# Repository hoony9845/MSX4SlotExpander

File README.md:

# MSX拡張Cartridge<BR>4Slot Expander Cartridge  

MSX スロットを4つに増やす拡張ユニットです。

> v2(バスバッファ付き・50pin IDCケーブル接続・大宇MSX後面スロット互換)の設計は [docs/expander_v2.md](./docs/expander_v2.md) を参照。

MSX規格の拡張スロット仕様に準拠した4スロットユニットです。  
信頼性が必要なカードエッジコネクタは、AMP 5530843-5または5530841-5を使用しています。  

Simple2Slot Expanderのサブセットで、本来の拡張スロットユニットに必要なバスバッファ・電源・音声ミキシング回路を省略することで安価になるように設計しました。  
そのため、個々のスロットは以下のMSX規格を守れていません。  

本基板および各オプションは、家電のKENちゃんおよびBEEPにて頒布を予定しています。    

## ■ 利用上の注意点  

構造上、誰がみても機械的に無理があるので縦差しでの使用はおすすめしません＾＾；  

バスバッファー回路が無い都合上、ファンアウトがMSXスロット規格を満たしていません、  
そのため本体およびカートリッジの組み合わせによる相性が出る場合があります。  

各スロットの電源容量は、本体に依存します。  
電力消費が大きいカートリッジでは動作しない可能性があります。  
規格上は合計で5V 100mAまでです、必要に応じて外部電源モードを使ってください。    
BUSDIR信号には対応しているので、IO系カセットも正常に動作します。

### 動作確認のスロット構成
当方の検証では下記機種、下記構成にて、全スロットへのRead/Writeが確認できています。
```
#X-1 ROM + Memory Mapper 1Mbyte
#X-2 DRAM 64K
#X-3 SCC Cartridge
#X-4 Flash ROM (TEST PROGRAM)
```
  
### 動作確認機種
MSX
- CASIO PV-16　（※外部電源モード）
- FUJITSU FM-X
- TOSHIBA HX-10
- Panasonic CF-1000
- Panasonic CF-3000  

MSX2  
- Panasonic FS-4600
- Panasonic FS-A1F
- TOSHIBA HX-34  
- D4D 1chip MSX

MSX2+
- SONY HB-F1XDJ
- SONY HB-F1XV
- SANYO WAVY 70

MSX Turbo R
- Panasonic FS-A1ST
- Panasonic FS-A1GT

### 不具合が合った機種
下記機種は、動作不良があった機種です。

MSX2  
- SONY HB-F500 　(オプションの延長ケーブルの使用時)
- SONY HB-F900 　(オプションの延長ケーブルの使用時)
- CANON V30

## ■ 頒布先
### 家電のKENちゃん
MSX Simple 4 Slot Expander【完成品】  
https://www.kadenken.com/view/item/000000001635  

●オプション  
加工済シェルケース(RGR製)  
クリアブラック　 :  https://www.kadenken.com/view/item/000000001318  
クリア　　　　 : https://www.kadenken.com/view/item/000000001317  

MSX Slot 延長ケーブル : https://www.kadenken.com/view/item/000000001636  

### BEEP
MSX Simple 4 Slot Expander【完成品】  
https://www.beep-shop.com/ec/products/detail/38517  

●オプション  
加工済シェルケース(RGR製)  
ブラック　　　 :  https://www.beep-shop.com/ec/products/detail/38515  
クリアブラック　 : https://www.beep-shop.com/ec/products/detail/38514  

MSX Slot 延長ケーブル : https://www.beep-shop.com/ec/products/detail/38516  

## ■ 付属品
本体には下記が付属しています。  
  
- ゴム足 　　　　　x 4個
- 専用スペーサー　　 x 2個
- タッピングビス(長)　 x 4個
- タッピングビス(短)　 x 4個  
### 付属品の使い方
直接本体のスロットに挿入する場合は、専用スペーサーをネジ止めして取り付けてください。  
オプションの延長ケーブルを使う場合は基板の裏面にゴム足を貼り付けて使用することも可能です。  
### 専用スペーサについて
固定には、スロットコネクタの左右の穴にタッピングビスを使って固定してください。

スロットコネクタは入手の都合で2種類あり、固定部があるものと無いものがあります。  
固定部があるものは長いタッピングビスを、無いものは短いタッピングビスを使って固定してください。  

使用時は脚部のネジを回して本体のスロットの高さに本製品を合わせてお使いください。

## ■ 使用方法

通常のカートリッジ同様に電源を切ったMSXスロットに挿入してください。  
カートリッジは、正面が下側になるように本基板スロットに挿入してください。

## ■ メモリマップ

MSXの拡張スロット仕様準拠です。

## ■ 頒布基板について
基板上のスイッチおよびジャンパの機能は下記の通りです。  

|Ref No|Name|機能|
| :- |  :- |  :- | 
|S1|SLTSEL(SLOT3)|SLOT3の切り離しスイッチです。<BR>つまみを下にするとカセットを切り離せます|
|S2|SLTSEL(SLOT2)|SLOT2の切り離しスイッチです。<BR>つまみを下にするとカセットを切り離せます|
|S3|SLTSEL(SLOT1)|SLOT1の切り離しスイッチです。<BR>つまみを下にするとカセットを切り離せます|
|S4|SLTSEL(SLOT0)|SLOT0の切り離しスイッチです。<BR>つまみを下にするとカセットを切り離せます|
|J5|POWER SETTING|スロットの5V電源を供給先を選択するジャンパです。<BR>INT側でMSX本体から、EXT側でDCジャックから供給します。|
|CN1 |DCジャック|Φ2.1 5Vセンタープラスのアダプタを接続します。|
|CN2 |SOUNDOUT（SLOT0)|SLOT0のサウンド出力です(オプション)|
|CN4 |SOUNDOUT（SLOT1)|SLOT1のサウンド出力です(オプション)|
|CN9 |SOUNDOUT（SLOT2)|SLOT2のサウンド出力です(オプション)|
|CN10 |SOUNDOUT（SLOT3)|SLOT3のサウンド出力です(オプション)|

回路図およびガーバファイルが必要な場合はPCBのフォルダーを参考にしてください。  

## ■ 外部電源供給について  
本製品はジャンパJ5を切り替えることでスロットの5V電源を外部供給に切り替えることが可能です。  
アダプタは、DCジャックは外径5.5mm内径2.1mm 電圧5V 500mA以上のアダプタを使用してください。  

下記の商品が使用できます。  

秋月電子　超小型スイッチングＡＣアダプター５Ｖ１Ａ  
https://akizukidenshi.com/catalog/g/gM-06096/

COMON DC-5521A + USB ACアダプタ   
http://www.comon.co.jp/DC-5521A.htm

## ■ サウンド出力について  
本製品はサウンドミキシング回路を搭載していません。SOUND IN端子は、4スロット間で直結しています。  
そのためサウンド出力を使うカートリッジを複数のスロットに挿さない様にしてください。
最悪の場合カートリッジを壊す可能性があります。

使用する場合はサウンド出力を使って、外部に接続したミキサーで音源を合成してください。  

### サウンド出力の使い方
DC入力近辺に、サウンド出力を追加するパターンを設けています。  
パーツは一般的なRCAジャックが使える様なパターンになっています。  
当該部にRCAジャックを半田付けしてください。  

推奨パーツ: 秋月電子　基板用ＲＣＡジャック（黒）  
https://akizukidenshi.com/catalog/g/gC-06509/

使用する場合は、J1-4 SOUNDジャンパの裏面パターンをカットしてください。  
裏面にジャンパを追加することで切り替え式にすることも可能です。(注意：表面だとカセットと接触します）  
なお、SLOT0のSOUNDジャンパ(J4)はシェルケールと干渉するので、そのまま使うのをおすすめします。  

### なぜミキシング回路をつけないのですか？
MSX本体の音声入力は規格で-5dbmと決められています。  
単純に4スロットの音声を全てミキシングしてしまうと出力は4倍になり規格違反になります。  
それを防ぐ為には、各スロットの音声を1/4する必要があるのですが、1つしか音声が入力を接続しないケースでは  
直接スロットに差すときと比較すると音声が非常に小さくなります。  
そこら辺の整合がとれないため、ミキシング回路は省略しています。

なお、市販されていたNEOS EX-4でもミキシング回路は入っておらず直結でした。

## ■ CPLDについて

CPLD Xillix XC9536XLの設計データはRTLのフォルダーを参照してください。  

## ■ (オプション)　MSXスロット延長ケーブル について
MSXのスロットを延長するケーブルです。(ケーブル長20cm)  
スロットに対する物理的な加重や構造的に無理がある場合にお使いください。  

なお本製品で使用しているカードエッジコネクタは大手メーカ製が廃盤になってしまっており、   
中国製のものを使用しています。そのため金メッキ品ですが長期信頼性は不明です。  
カートリッジシェルは本製品と同じものが使用できます。

使用時はコネクタに張ってある、シール側がカセット正面になるようにセットしてください。

## ■ (オプション)カートリッジシェル について
シェルケースは
RGRさんのTransparent Cartridge Shell for MSX Konami-styleを切削加工したものを使用しています。  
<https://retrogamerestore.com/store/msx_cart_shell/>  

当方でも加工済みシェルを用意しており、委託先で購入が可能です。  
輸入と加工の都合で若干の小傷がある場合があります。あらかじめご了承ください。  

切削加工部分については、下記図面を参照ください。（ハッチ部分が切削箇所）

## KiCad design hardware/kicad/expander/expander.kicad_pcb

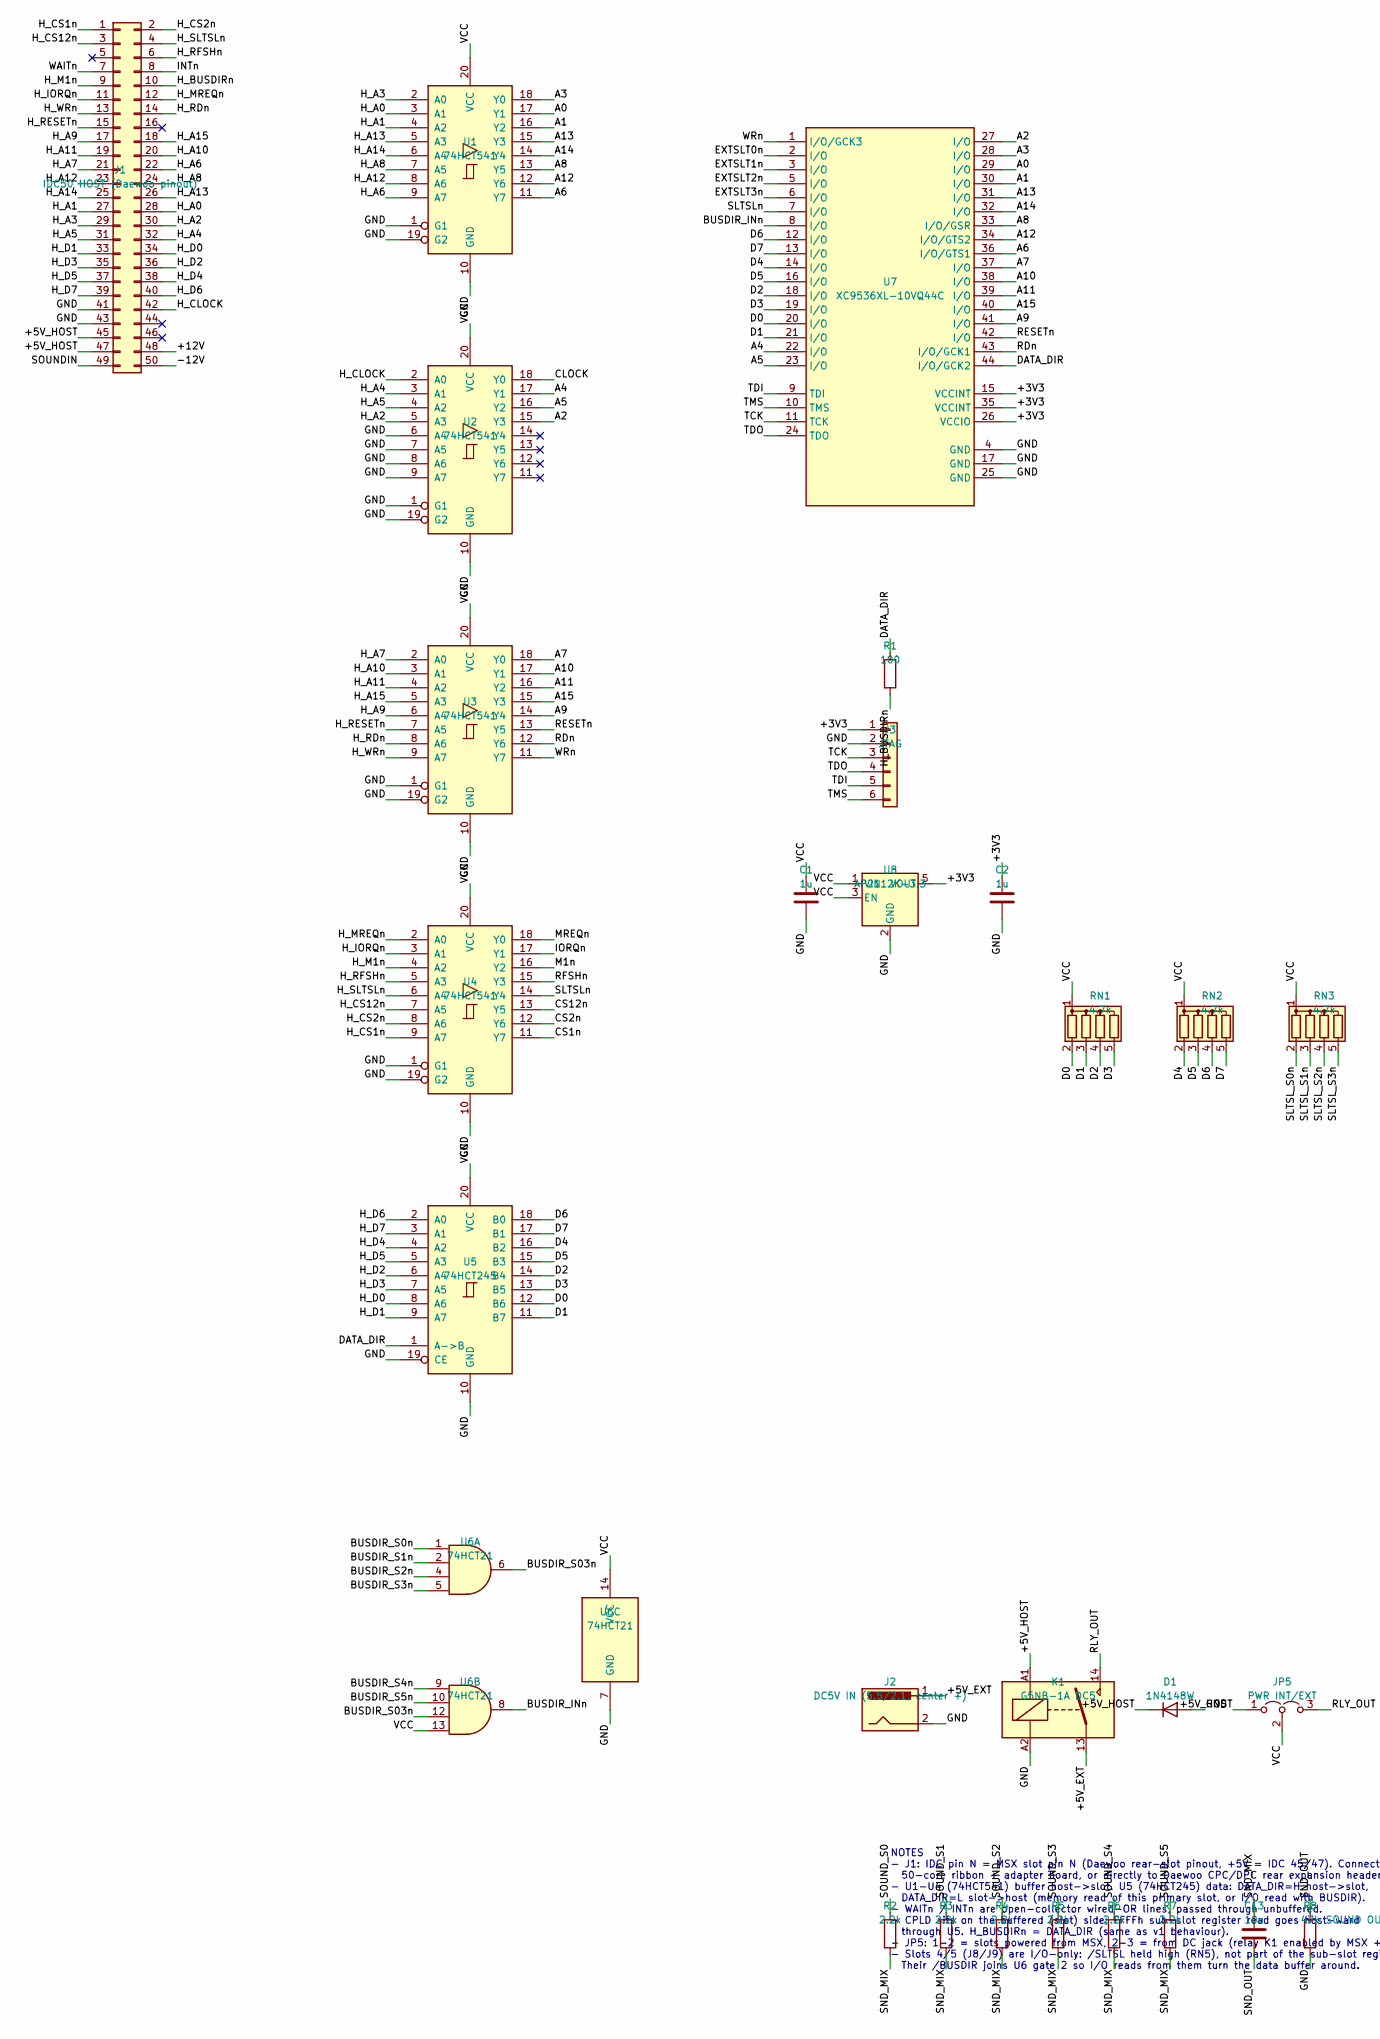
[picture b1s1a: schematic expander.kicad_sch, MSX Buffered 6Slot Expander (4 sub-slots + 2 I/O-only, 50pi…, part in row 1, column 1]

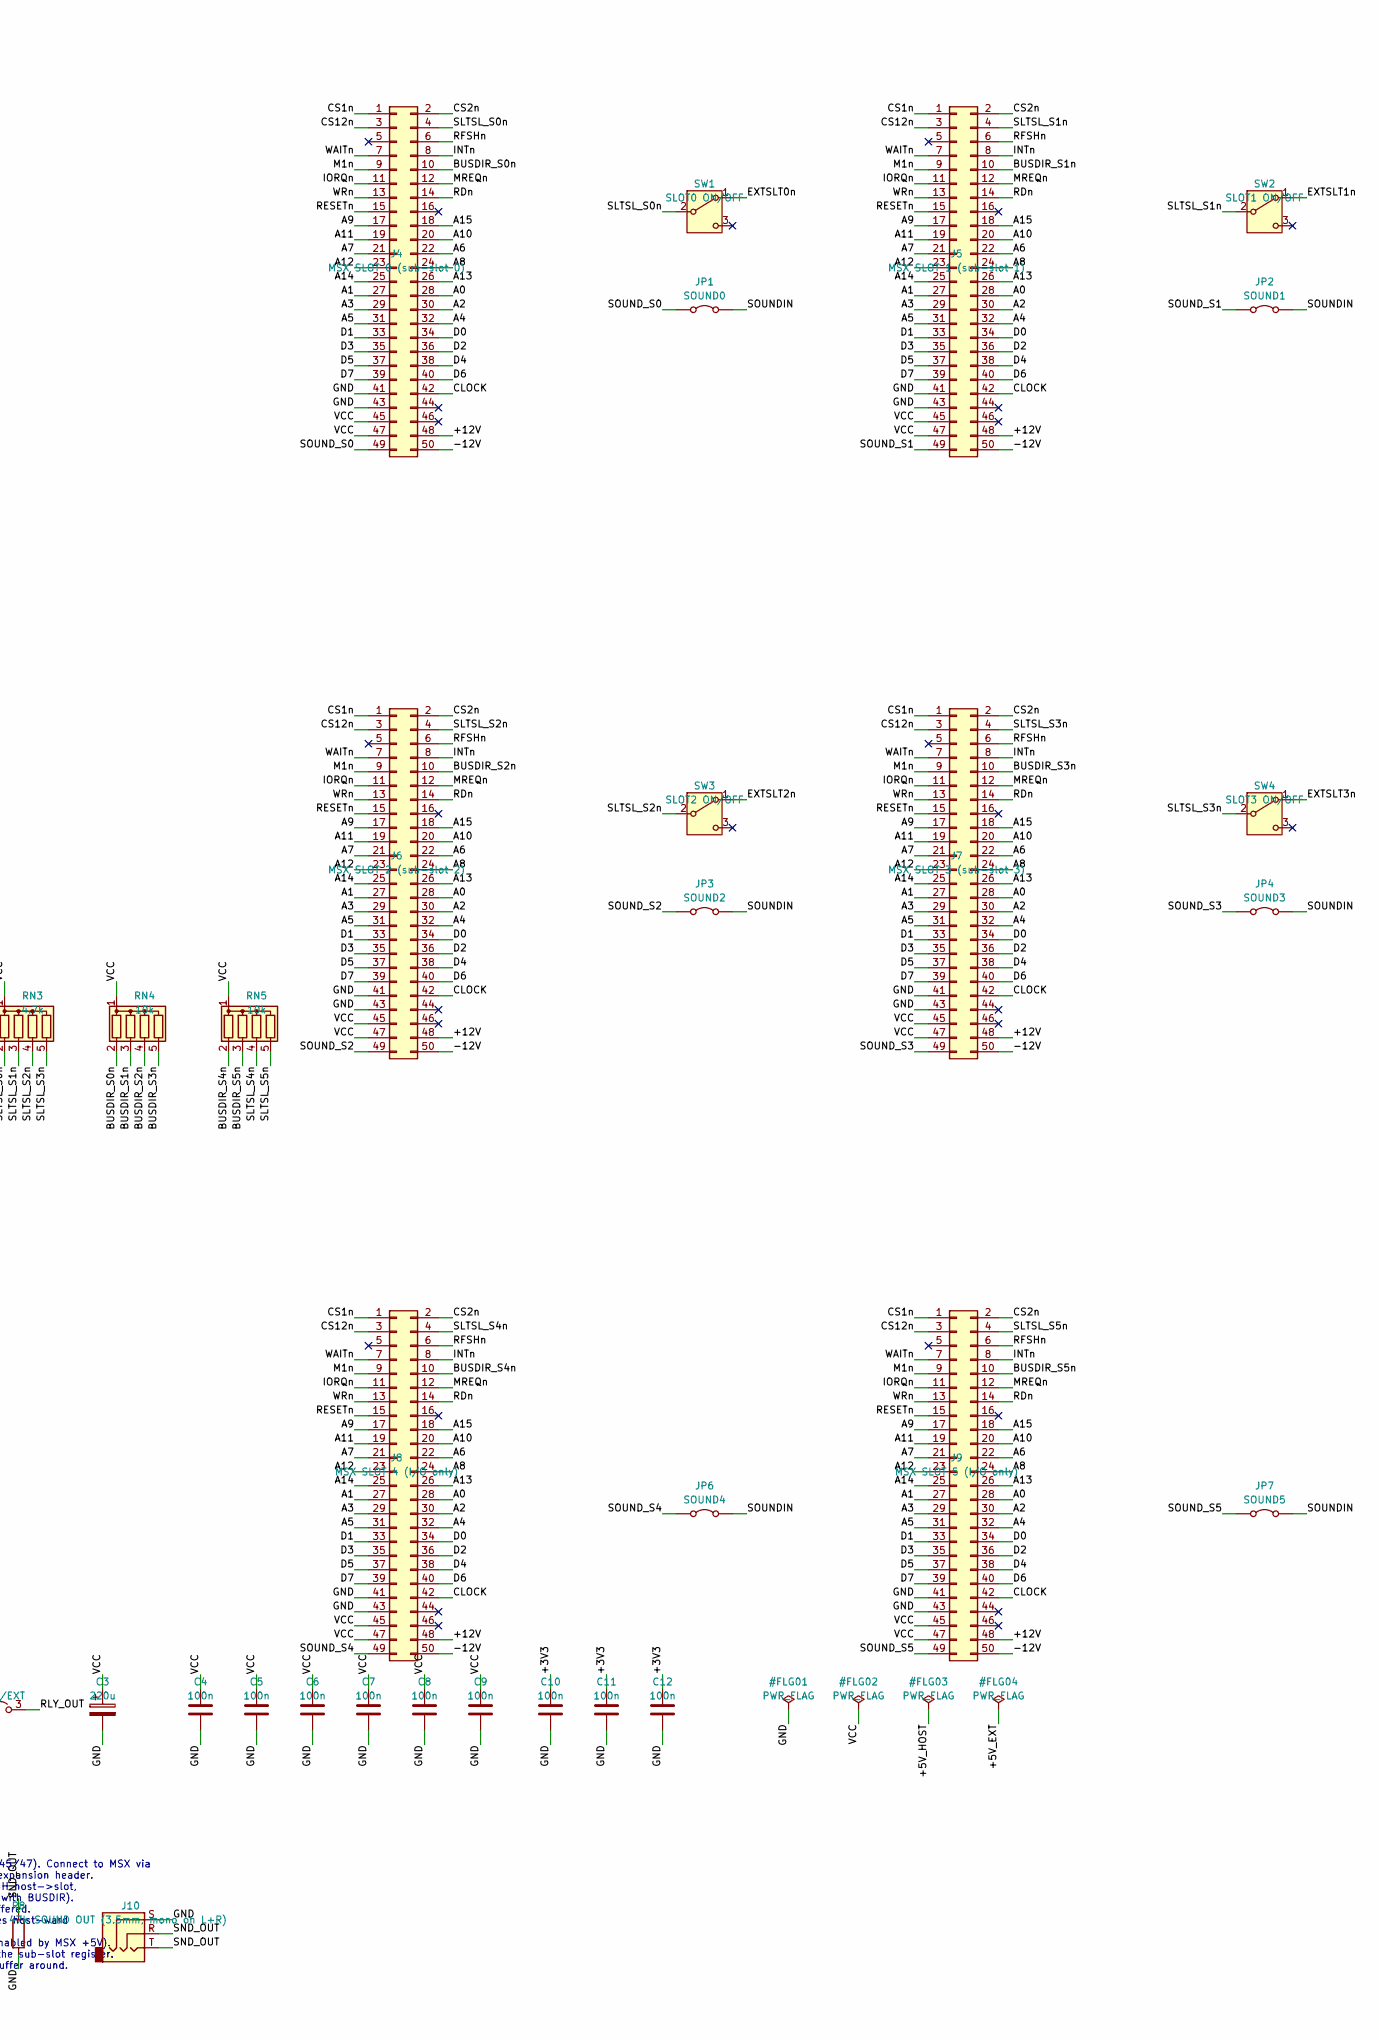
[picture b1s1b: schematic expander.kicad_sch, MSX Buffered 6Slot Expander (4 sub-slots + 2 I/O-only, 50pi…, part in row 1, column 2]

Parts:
C1, C2: 1u; C_0805_2012Metric
C3: 220u; CP_Radial_D6.3mm_P2.50mm
C4, C5, C6, C7, C8, C9, C10, C11, C12: 100n; C_0805_2012Metric
C13: 10u; C_0805_2012Metric
D1: 1N4148W; D_SOD-123
J1: IDC50 HOST (Daewoo pinout); IDC-Header_2x25_P2.54mm_Horizontal_OddRowFront
J2: DC5V IN (5.5/2.1, center +); BarrelJack_Horizontal
J3: JTAG; PinHeader_1x06_P2.54mm_Vertical
J4: MSX SLOT 0 (sub-slot 0); MSX_Slot_AMP5530843
J5: MSX SLOT 1 (sub-slot 1); MSX_Slot_AMP5530843
J6: MSX SLOT 2 (sub-slot 2); MSX_Slot_AMP5530843
J7: MSX SLOT 3 (sub-slot 3); MSX_Slot_AMP5530843
J8: MSX SLOT 4 (I/O only); MSX_Slot_AMP5530843
J9: MSX SLOT 5 (I/O only); MSX_Slot_AMP5530843
J10: SOUND OUT (3.5mm, mono on L+R); Jack_3.5mm_CUI_SJ1-3523N_Horizontal
JP1: SOUND0; PinHeader_1x02_P2.54mm_Vertical
JP2: SOUND1; PinHeader_1x02_P2.54mm_Vertical
JP3: SOUND2; PinHeader_1x02_P2.54mm_Vertical
JP4: SOUND3; PinHeader_1x02_P2.54mm_Vertical
JP5: PWR INT/EXT; PinHeader_1x03_P2.54mm_Vertical
JP6: SOUND4; PinHeader_1x02_P2.54mm_Vertical
JP7: SOUND5; PinHeader_1x02_P2.54mm_Vertical
K1: G5NB-1A DC5; Relay_SPST_Omron_G5NB
R1: 100; R_0805_2012Metric
R2, R3, R4, R5, R6, R7: 2.2k; R_0805_2012Metric
R8: 47k; R_0805_2012Metric
RN1, RN2, RN3: 4.7k; R_Array_SIP5
RN4, RN5: 10k; R_Array_SIP5
SW1: SLOT0 ON/OFF; SW_Slide_SPDT_Angled_CK_OS102011MA1Q
SW2: SLOT1 ON/OFF; SW_Slide_SPDT_Angled_CK_OS102011MA1Q
SW3: SLOT2 ON/OFF; SW_Slide_SPDT_Angled_CK_OS102011MA1Q
SW4: SLOT3 ON/OFF; SW_Slide_SPDT_Angled_CK_OS102011MA1Q
U1, U2, U3, U4: 74HCT541; SOIC-20W_7.5x12.8mm_P1.27mm
U5: 74HCT245; SOIC-20W_7.5x12.8mm_P1.27mm
U6: 74HCT21; SOIC-14_3.9x8.7mm_P1.27mm
U7: XC9536XL-10VQ44C; TQFP-44_10x10mm_P0.8mm
U8: AP2112K-3.3; SOT-23-5

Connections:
/+3V3: C2.1, C10.1, C11.1, C12.1, J3.1, U7.15 (VCCINT), U7.26 (VCCIO), U7.35 (VCCINT), U8.5 (VOUT)
/+5V_EXT: J2.1, K1.13
/+5V_HOST: D1.1 (K), J1.45, J1.47, JP5.1 (A), K1.A1
/+12V: J1.48, J4.48, J5.48, J6.48, J7.48, J8.48, J9.48
/-12V: J1.50, J4.50, J5.50, J6.50, J7.50, J8.50, J9.50
/A0: J4.28, J5.28, J6.28, J7.28, J8.28, J9.28, U1.17 (Y1), U7.29 (I/O)
/A1: J4.27, J5.27, J6.27, J7.27, J8.27, J9.27, U1.16 (Y2), U7.30 (I/O)
/A2: J4.30, J5.30, J6.30, J7.30, J8.30, J9.30, U2.15 (Y3), U7.27 (I/O)
/A3: J4.29, J5.29, J6.29, J7.29, J8.29, J9.29, U1.18 (Y0), U7.28 (I/O)
/A4: J4.32, J5.32, J6.32, J7.32, J8.32, J9.32, U2.17 (Y1), U7.22 (I/O)
/A5: J4.31, J5.31, J6.31, J7.31, J8.31, J9.31, U2.16 (Y2), U7.23 (I/O)
/A6: J4.22, J5.22, J6.22, J7.22, J8.22, J9.22, U1.11 (Y7), U7.36 (I/O/GTS1)
/A7: J4.21, J5.21, J6.21, J7.21, J8.21, J9.21, U3.18 (Y0), U7.37 (I/O)
/A8: J4.24, J5.24, J6.24, J7.24, J8.24, J9.24, U1.13 (Y5), U7.33 (I/O/GSR)
/A9: J4.17, J5.17, J6.17, J7.17, J8.17, J9.17, U3.14 (Y4), U7.41 (I/O)
/A10: J4.20, J5.20, J6.20, J7.20, J8.20, J9.20, U3.17 (Y1), U7.38 (I/O)
/A11: J4.19, J5.19, J6.19, J7.19, J8.19, J9.19, U3.16 (Y2), U7.39 (I/O)
/A12: J4.23, J5.23, J6.23, J7.23, J8.23, J9.23, U1.12 (Y6), U7.34 (I/O/GTS2)
/A13: J4.26, J5.26, J6.26, J7.26, J8.26, J9.26, U1.15 (Y3), U7.31 (I/O)
/A14: J4.25, J5.25, J6.25, J7.25, J8.25, J9.25, U1.14 (Y4), U7.32 (I/O)
/A15: J4.18, J5.18, J6.18, J7.18, J8.18, J9.18, U3.15 (Y3), U7.40 (I/O)
/BUSDIR_INn: U6.8, U7.8 (I/O)
/BUSDIR_S0n: J4.10, RN4.2 (R1), U6.1
/BUSDIR_S1n: J5.10, RN4.3 (R2), U6.2
/BUSDIR_S2n: J6.10, RN4.4 (R3), U6.4
/BUSDIR_S3n: J7.10, RN4.5 (R4), U6.5
/BUSDIR_S03n: U6.6, U6.12
/BUSDIR_S4n: J8.10, RN5.2 (R1), U6.9
/BUSDIR_S5n: J9.10, RN5.3 (R2), U6.10
/CLOCK: J4.42, J5.42, J6.42, J7.42, J8.42, J9.42, U2.18 (Y0)
/CS1n: J4.1, J5.1, J6.1, J7.1, J8.1, J9.1, U4.11 (Y7)
/CS2n: J4.2, J5.2, J6.2, J7.2, J8.2, J9.2, U4.12 (Y6)
/CS12n: J4.3, J5.3, J6.3, J7.3, J8.3, J9.3, U4.13 (Y5)
/D0: J4.34, J5.34, J6.34, J7.34, J8.34, J9.34, RN1.2 (R1), U5.12 (B6), U7.20 (I/O)
/D1: J4.33, J5.33, J6.33, J7.33, J8.33, J9.33, RN1.3 (R2), U5.11 (B7), U7.21 (I/O)
/D2: J4.36, J5.36, J6.36, J7.36, J8.36, J9.36, RN1.4 (R3), U5.14 (B4), U7.18 (I/O)
/D3: J4.35, J5.35, J6.35, J7.35, J8.35, J9.35, RN1.5 (R4), U5.13 (B5), U7.19 (I/O)
/D4: J4.38, J5.38, J6.38, J7.38, J8.38, J9.38, RN2.2 (R1), U5.16 (B2), U7.14 (I/O)
/D5: J4.37, J5.37, J6.37, J7.37, J8.37, J9.37, RN2.3 (R2), U5.15 (B3), U7.16 (I/O)
/D6: J4.40, J5.40, J6.40, J7.40, J8.40, J9.40, RN2.4 (R3), U5.18 (B0), U7.12 (I/O)
/D7: J4.39, J5.39, J6.39, J7.39, J8.39, J9.39, RN2.5 (R4), U5.17 (B1), U7.13 (I/O)
/DATA_DIR: R1.1, U5.1 (A->B), U7.44 (I/O/GCK2)
/EXTSLT0n: SW1.1 (A), U7.2 (I/O)
/EXTSLT1n: SW2.1 (A), U7.3 (I/O)
/EXTSLT2n: SW3.1 (A), U7.5 (I/O)
/EXTSLT3n: SW4.1 (A), U7.6 (I/O)
/GND: C1.2, C2.2, C3.2, C4.2, C5.2, C6.2, C7.2, C8.2, C9.2, C10.2, C11.2, C12.2, D1.2 (A), J1.41, J1.43, J2.2, J3.2, J4.41, J4.43, J5.41, J5.43, J6.41, J6.43, J7.41, J7.43, J8.41, J8.43, J9.41, J9.43, J10.S, K1.A2, R8.2, U1.1 (G1), U1.10 (GND), U1.19 (G2), U2.1 (G1), U2.6 (A4), U2.7 (A5), U2.8 (A6), U2.9 (A7), U2.10 (GND), U2.19 (G2), U3.1 (G1), U3.10 (GND), U3.19 (G2), U4.1 (G1), U4.10 (GND), U4.19 (G2), U5.10 (GND), U5.19 (CE), U6.7 (GND), U7.4 (GND), U7.17 (GND), U7.25 (GND), U8.2 (GND)
/H_A0: J1.28, U1.3 (A1)
/H_A1: J1.27, U1.4 (A2)
/H_A2: J1.30, U2.5 (A3)
/H_A3: J1.29, U1.2 (A0)
/H_A4: J1.32, U2.3 (A1)
/H_A5: J1.31, U2.4 (A2)
/H_A6: J1.22, U1.9 (A7)
/H_A7: J1.21, U3.2 (A0)
/H_A8: J1.24, U1.7 (A5)
/H_A9: J1.17, U3.6 (A4)
/H_A10: J1.20, U3.3 (A1)
/H_A11: J1.19, U3.4 (A2)
/H_A12: J1.23, U1.8 (A6)
/H_A13: J1.26, U1.5 (A3)
/H_A14: J1.25, U1.6 (A4)
/H_A15: J1.18, U3.5 (A3)
/H_BUSDIRn: J1.10, R1.2
/H_CLOCK: J1.42, U2.2 (A0)
/H_CS1n: J1.1, U4.9 (A7)
/H_CS2n: J1.2, U4.8 (A6)
/H_CS12n: J1.3, U4.7 (A5)
/H_D0: J1.34, U5.8 (A6)
/H_D1: J1.33, U5.9 (A7)
/H_D2: J1.36, U5.6 (A4)
/H_D3: J1.35, U5.7 (A5)
/H_D4: J1.38, U5.4 (A2)
/H_D5: J1.37, U5.5 (A3)
/H_D6: J1.40, U5.2 (A0)
/H_D7: J1.39, U5.3 (A1)
/H_IORQn: J1.11, U4.3 (A1)
/H_M1n: J1.9, U4.4 (A2)
/H_MREQn: J1.12, U4.2 (A0)
/H_RDn: J1.14, U3.8 (A6)
/H_RESETn: J1.15, U3.7 (A5)
/H_RFSHn: J1.6, U4.5 (A3)
/H_SLTSLn: J1.4, U4.6 (A4)
/H_WRn: J1.13, U3.9 (A7)
/INTn: J1.8, J4.8, J5.8, J6.8, J7.8, J8.8, J9.8
/IORQn: J4.11, J5.11, J6.11, J7.11, J8.11, J9.11, U4.17 (Y1)
/M1n: J4.9, J5.9, J6.9, J7.9, J8.9, J9.9, U4.16 (Y2)
/MREQn: J4.12, J5.12, J6.12, J7.12, J8.12, J9.12, U4.18 (Y0)
/RDn: J4.14, J5.14, J6.14, J7.14, J8.14, J9.14, U3.12 (Y6), U7.43 (I/O/GCK1)
/RESETn: J4.15, J5.15, J6.15, J7.15, J8.15, J9.15, U3.13 (Y5), U7.42 (I/O)
/RFSHn: J4.6, J5.6, J6.6, J7.6, J8.6, J9.6, U4.15 (Y3)
/RLY_OUT: JP5.3 (B), K1.14
/SLTSL_S0n: J4.4, RN3.2 (R1), SW1.2 (B)
/SLTSL_S1n: J5.4, RN3.3 (R2), SW2.2 (B)
/SLTSL_S2n: J6.4, RN3.4 (R3), SW3.2 (B)
/SLTSL_S3n: J7.4, RN3.5 (R4), SW4.2 (B)
/SLTSL_S4n: J8.4, RN5.4 (R3)
/SLTSL_S5n: J9.4, RN5.5 (R4)
/SLTSLn: U4.14 (Y4), U7.7 (I/O)
/SND_MIX: C13.1, R2.2, R3.2, R4.2, R5.2, R6.2, R7.2
/SND_OUT: C13.2, J10.R, J10.T, R8.1
/SOUNDIN: J1.49, JP1.2 (B), JP2.2 (B), JP3.2 (B), JP4.2 (B), JP6.2 (B), JP7.2 (B)
/SOUND_S0: J4.49, JP1.1 (A), R2.1
/SOUND_S1: J5.49, JP2.1 (A), R3.1
/SOUND_S2: J6.49, JP3.1 (A), R4.1
/SOUND_S3: J7.49, JP4.1 (A), R5.1
/SOUND_S4: J8.49, JP6.1 (A), R6.1
/SOUND_S5: J9.49, JP7.1 (A), R7.1
/TCK: J3.3, U7.11 (TCK)
/TDI: J3.5, U7.9 (TDI)
/TDO: J3.4, U7.24 (TDO)
/TMS: J3.6, U7.10 (TMS)
/VCC: C1.1, C3.1, C4.1, C5.1, C6.1, C7.1, C8.1, C9.1, J4.45, J4.47, J5.45, J5.47, J6.45, J6.47, J7.45, J7.47, J8.45, J8.47, J9.45, J9.47, JP5.2 (C), RN1.1 (common), RN2.1 (common), RN3.1 (common), RN4.1 (common), RN5.1 (common), U1.20 (VCC), U2.20 (VCC), U3.20 (VCC), U4.20 (VCC), U5.20 (VCC), U6.13, U6.14 (VCC), U8.1 (VIN), U8.3 (EN)
/WAITn: J1.7, J4.7, J5.7, J6.7, J7.7, J8.7, J9.7
/WRn: J4.13, J5.13, J6.13, J7.13, J8.13, J9.13, U3.11 (Y7), U7.1 (I/O/GCK3)

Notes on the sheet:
NOTES - J1: IDC pin N = MSX slot pin N (Daewoo rear-slot pinout, +5V = IDC 45/47). Connect to MSX via 50-core ribbon + adapter board, or directly to Daewoo CPC/DPC rear expansion header. - U1-U4 (74HCT541) buffer host->slot. U5 (74HCT245) data: DATA_DIR=H host->slot, DATA_DIR=L slot->host (memory r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

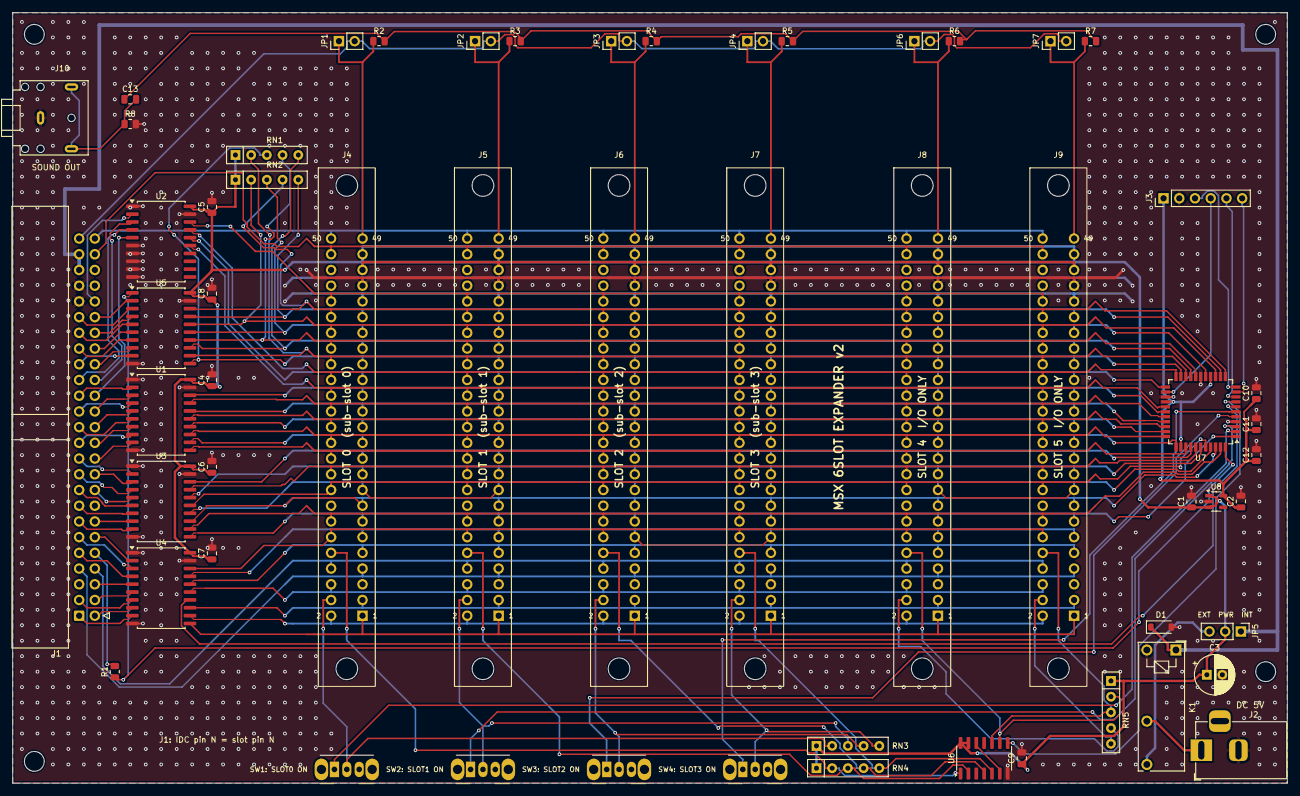
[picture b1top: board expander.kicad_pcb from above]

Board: 2 copper layers, 206.0 x 124.5 mm, 57 parts (0 on the bottom side), 115 nets.

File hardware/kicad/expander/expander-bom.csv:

"Refs","Value","Footprint","Qty"
"C1,C2","1u","Capacitor_SMD:C_0805_2012Metric","2"
"C3","220u","Capacitor_THT:CP_Radial_D6.3mm_P2.50mm","1"
"C4-C12","100n","Capacitor_SMD:C_0805_2012Metric","9"
"C13","10u","Capacitor_SMD:C_0805_2012Metric","1"
"D1","1N4148W","Diode_SMD:D_SOD-123","1"
"J1","IDC50 HOST (Daewoo pinout)","MSXExp:IDC-Header_2x25_P2.54mm_Horizontal_OddRowFront","1"
"J2","DC5V IN (5.5/2.1, center +)","Connector_BarrelJack:BarrelJack_Horizontal","1"
"J3","JTAG","Connector_PinHeader_2.54mm:PinHeader_1x06_P2.54mm_Vertical","1"
"J4","MSX SLOT 0 (sub-slot 0)","MSXExp:MSX_Slot_AMP5530843","1"
"J5","MSX SLOT 1 (sub-slot 1)","MSXExp:MSX_Slot_AMP5530843","1"
"J6","MSX SLOT 2 (sub-slot 2)","MSXExp:MSX_Slot_AMP5530843","1"
"J7","MSX SLOT 3 (sub-slot 3)","MSXExp:MSX_Slot_AMP5530843","1"
"J8","MSX SLOT 4 (I/O only)","MSXExp:MSX_Slot_AMP5530843","1"
"J9","MSX SLOT 5 (I/O only)","MSXExp:MSX_Slot_AMP5530843","1"
"J10","SOUND OUT (3.5mm, mono on L+R)","Connector_Audio:Jack_3.5mm_CUI_SJ1-3523N_Horizontal","1"
"JP1","SOUND0","Connector_PinHeader_2.54mm:PinHeader_1x02_P2.54mm_Vertical","1"
"JP2","SOUND1","Connector_PinHeader_2.54mm:PinHeader_1x02_P2.54mm_Vertical","1"
"JP3","SOUND2","Connector_PinHeader_2.54mm:PinHeader_1x02_P2.54mm_Vertical","1"
"JP4","SOUND3","Connector_PinHeader_2.54mm:PinHeader_1x02_P2.54mm_Vertical","1"
"JP5","PWR INT/EXT","Connector_PinHeader_2.54mm:PinHeader_1x03_P2.54mm_Vertical","1"
"JP6","SOUND4","Connector_PinHeader_2.54mm:PinHeader_1x02_P2.54mm_Vertical","1"
"JP7","SOUND5","Connector_PinHeader_2.54mm:PinHeader_1x02_P2.54mm_Vertical","1"
"K1","G5NB-1A DC5","Relay_THT:Relay_SPST_Omron_G5NB","1"
"R1","100","Resistor_SMD:R_0805_2012Metric","1"
"R2-R7","2.2k","Resistor_SMD:R_0805_2012Metric","6"
"R8","47k","Resistor_SMD:R_0805_2012Metric","1"
"RN1-RN3","4.7k","Resistor_THT:R_Array_SIP5","3"
"RN4,RN5","10k","Resistor_THT:R_Array_SIP5","2"
"SW1","SLOT0 ON/OFF","Button_Switch_THT:SW_Slide_SPDT_Angled_CK_OS102011MA1Q","1"
"SW2","SLOT1 ON/OFF","Button_Switch_THT:SW_Slide_SPDT_Angled_CK_OS102011MA1Q","1"
"SW3","SLOT2 ON/OFF","Button_Switch_THT:SW_Slide_SPDT_Angled_CK_OS102011MA1Q","1"
"SW4","SLOT3 ON/OFF","Button_Switch_THT:SW_Slide_SPDT_Angled_CK_OS102011MA1Q","1"
"U1-U4","74HCT541","Package_SO:SOIC-20W_7.5x12.8mm_P1.27mm","4"
"U5","74HCT245","Package_SO:SOIC-20W_7.5x12.8mm_P1.27mm","1"
"U6","74HCT21","Package_SO:SOIC-14_3.9x8.7mm_P1.27mm","1"
"U7","XC9536XL-10VQ44C","Package_QFP:TQFP-44_10x10mm_P0.8mm","1"
"U8","AP2112K-3.3","Package_TO_SOT_SMD:SOT-23-5","1"

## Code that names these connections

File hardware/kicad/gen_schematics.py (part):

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_CPLD_SLOTS = [12, 13, 14, 16, 18, 19, 20, 21, 22, 23, 27, 28, 29, 30, 31, 32, 33, 34,
               36, 37, 38, 39, 40, 41, 42, 43]
CPLD_PINS = {str(p): n for p, n in zip(_CPLD_SLOTS, _CPLD_ORDER)}
CPLD_PINS.update({"1": "WRn", "44": "DATA_DIR", "2": "EXTSLT0n", "3": "EXTSLT1n",
                  "5": "EXTSLT2n", "6": "EXTSLT3n", "7": "SLTSLn", "8": "BUSDIR_INn"})


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    groups = [
        ["A3", "A0", "A1", "A13", "A14", "A8", "A12", "A6"],             # U1: slot pins 29..22
        ["CLOCK", "A4", "A5", "A2", None, None, None, None],             # U2: pins 42, 32..30
        ["A7", "A10", "A11", "A15", "A9", "RESETn", "RDn", "WRn"],       # U3: pins 21..13
        ["MREQn", "IORQn", "M1n", "RFSHn", "SLTSLn", "CS12n", "CS2n", "CS1n"],  # U4: pins 12..1
    ]
    for i, g in enumerate(groups):
        nets = {"1": "GND", "19": "GND", "10": "GND", "20": "VCC"}
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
